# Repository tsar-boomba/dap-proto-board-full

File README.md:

# Bomb DAP Full Proto Board

The culmination of all of my learning during the Spring '26 semester. All the way from making a simple dev board for the TAD5212 DAC, to making a RP2350 board, and now this. Everything combined on one 6-layer board.

# V1 Pinouts

- GPIO0 -> PSRAM_CS
- GPIO1 -> npm1300 GPIO0
- GPIO2 -> DISP_IO_ON (level-shifter enable)
- GPIO3 -> Display Backlight
- GPIO4 -> Display SCLK (PIO SPI)
- GPIO5 -> Display MOSI (PIO SPI)
- GPIO6 -> Display MISO (PIO SPI)
- GPIO7 -> Display DC & SDA
- GPIO8 -> Display CS & SCL
- GPIO(9-11) -> Broken out
- GPIO12 -> SD MISO (SPI1)
- GPIO13 -> SD CS
- GPIO14 -> SD SCLK (SPI1)
- GPIO15 -> SD MOSI (SPI1)
- GPIO16 -> npm1300 SDA (I2C0)
- GPIO17 -> npm1300 SCL (I2C0)
- GPIO18 -> SD ON (load switch & level-shifter enable)
- GPIO19 -> TAD GPIO1
- GPIO20 -> TAD SDA (PIO I2C)
- GPIO21 -> TAD SCL (PIO I2C)
- GPIO(22-26) -> Broken out
- GPIO27 -> TAD DIN (PIO I2S)
- GPIO28 -> TAD FSYNC (PIO I2S)
- GPIO29 -> TAD BCLK (PIO I2S)

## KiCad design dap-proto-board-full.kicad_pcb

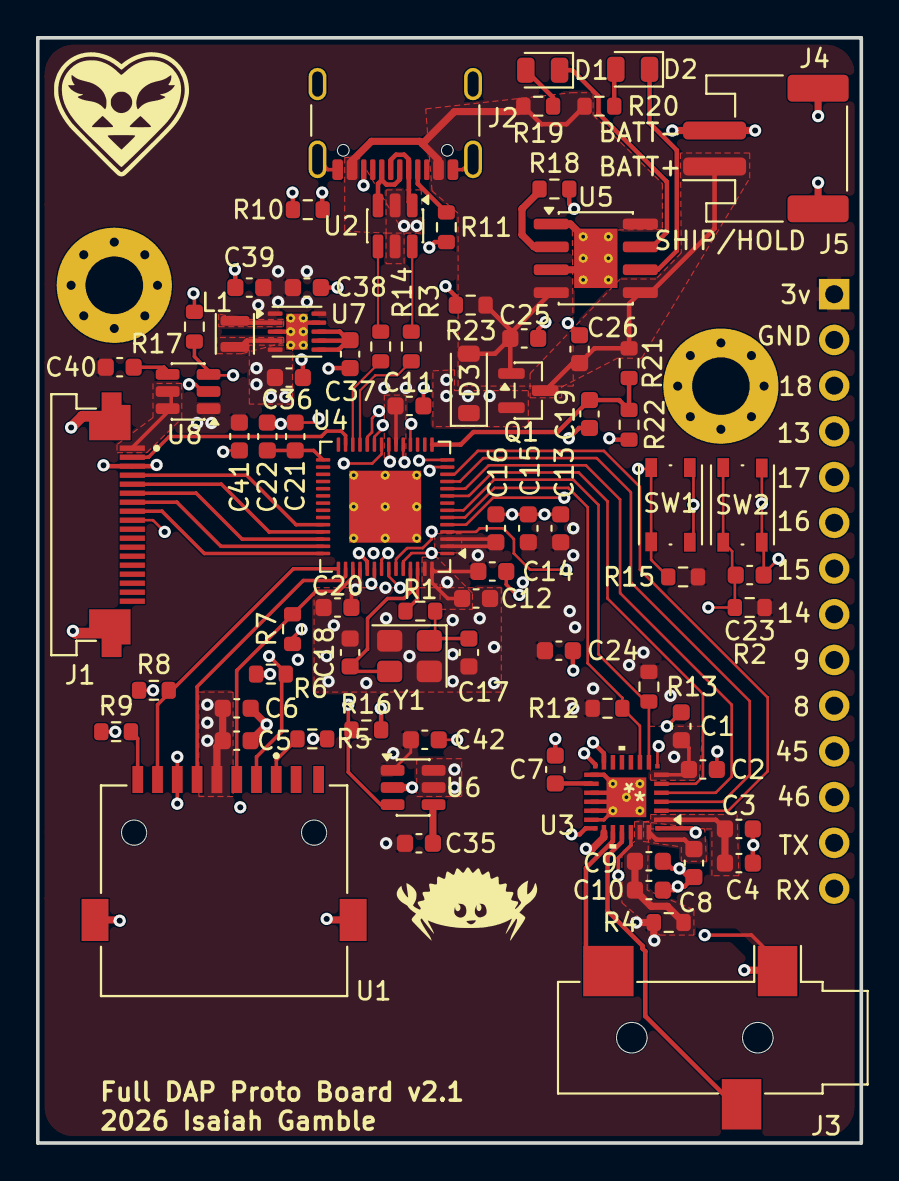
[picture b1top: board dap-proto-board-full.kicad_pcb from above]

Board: 4 copper layers, 45.8 x 61.4 mm, 80 parts (0 on the bottom side), 70 nets.

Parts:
C1, C3, C5, C9, C11, C16, C19, C20, C22, C37: 100nF; C_0603_1608Metric
C2, C4, C6, C10, C24, C26, C38, C39: 10uF; C_0603_1608Metric
C7, C8, C12, C15, C21, C23, C41, C42: 1uF; C_0603_1608Metric
C13: 22uF; C_0603_1608Metric
C14: 10nF; C_0603_1608Metric
C17, C18: 15pF; C_0603_1608Metric
C25, C36: 4.7uF; C_0603_1608Metric
C35, C40: 1nF; C_0603_1608Metric
D1: Yellow; LED_0805_2012Metric
D2: Green; LED_0805_2012Metric
D3: B5819W SL; D_SOD-123
H1, H2: MountingHole_Pad; MountingHole_3.2mm_M3_Pad_Via
J1: SFV18R-1STE1HLF; AMPHENOL_SFV18R-1STE1HLF
J2: UJ20-C-H-G-SMT-1-P16-TR; USB_C_Receptacle_GCT_USB4105-xx-A_16P_TopMnt_Horizontal
J3: SJ-3523-SMT-TR; Jack_3.5mm_CUI_SJ-3523-SMT_Horizontal
J4: S2B-PH-SM4-TB(LF)(SN); JST_PH_S2B-PH-SM4-TB_1x02-1MP_P2.00mm_Horizontal
J5: Conn_01x14; PinSocket_1x14_P2.54mm_Vertical
L1: 1.5uH; L_Murata_DFE201610P
Q1: AO3401A; SOT-23
R1, R4: 0; R_0603_1608Metric
R2, R5, R6, R7, R8, R9, R12, R13, R15, R23: 10k; R_0603_1608Metric
R3, R14: 22; R_0603_1608Metric
R10, R11: 5.1k; R_0603_1608Metric
R16, R17: 100k; R_0603_1608Metric
R18: 3k; R_0603_1608Metric
R19, R20: 1k; R_0603_1608Metric
R21: 1M; R_0603_1608Metric
R22: 470k; R_0603_1608Metric
SW1, SW2: SW_Push; SW_Push_1P1T_NO_Vertical_Wuerth_434133025816
U1: MSD-11-A; CUI_MSD-11-A
U2: USBLC6-2SC6; SOT-23-6
U3: TAD5212; VQFN24_RGE_CORNERPADS_TEX
U4: ESP32-S3FH4R2; QFN-56-1EP_7x7mm_P0.4mm_EP4x4mm_ThermalVias
U5: TP4056-42-ESOP8; SOIC-8-1EP_3.9x4.9mm_P1.27mm_EP2.41x3.3mm_ThermalVias
U6, U8: TPS22917DBVR; SOT-23-6
U7: TPS63031DSKR; WSON-10-1EP_2.5x2.5mm_P0.5mm_EP1.2x2mm_ThermalVias
Y1: TSX-3225 40.0000MF15Y-K3; Crystal_SMD_3225-4Pin_3.2x2.5mm

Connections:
+3V3: C1.2, C2.1, C11.1, C12.1, C13.1, C14.1, C15.1, C16.1, C20.1, C24.1, C35.1, C38.1, C39.1, C40.1, C41.1, C42.1, J5.1, R2.1, R4.1, R12.1, R13.1, R15.1, U3.6 (IOVDD), U4.2 (VDD3P3), U4.3 (VDD3P3), U4.20 (VDD3P3_RTC), U4.46 (VDD3P3_CPU), U4.55 (VDDA), U4.56 (VDDA), U6.1 (VIN), U7.1 (VOUT), U7.10 (FB), U8.1 (VIN)
+BATT: C26.1, J4.1, Q1.3 (D), R21.1, U5.5 (BAT)
/BATT_SENSE: C19.1, R21.2, R22.1, U4.15 (GPIO10)
/BCLK: U3.2 (BCLK), U4.12 (GPIO7)
/DIN: U3.5 (DIN), U4.9 (GPIO4)
/DISP_ON: R17.1, U4.22 (XTAL_32K_N), U8.3 (ON)
/DOUT: U3.4 (DOUT), U4.10 (GPIO5)
/DREG: C3.2, C4.1, U3.1 (DREG)
/FSYNC: U3.3 (FSYNC), U4.11 (GPIO6)
/GPIO8: J5.10, U4.13 (GPIO8)
/GPIO9: J5.9, U4.14 (GPIO9)
/GPIO13: J5.4, U4.18 (GPIO13)
/GPIO14: J5.8, U4.19 (GPIO14)
/GPIO17: J5.5, U4.23 (GPIO17)
/GPIO18: J5.3, U4.24 (GPIO18)
/GPIO45: J5.11, U4.51 (GPIO45)
/GPIO46: J5.12, U4.52 (GPIO46)
/OUT1P: J3.T, U3.20 (OUT1P)
/OUT2P: J3.R, U3.21 (OUT2P)
/SD_CS: R6.2, U1.2 (CS), U4.47 (MTDI)
/SD_DAT1: R9.2, U1.8 (DAT1)
/SD_DAT2: R5.2, U1.1 (DAT2)
/SD_DIN: R7.2, U1.3 (DATA_IN), U4.45 (MTDO)
/SD_DOUT: R8.2, U1.7 (DATA_OUT), U4.43 (GPIO38)
/SD_ON: R16.1, U4.48 (MTMS), U6.3 (ON)
/SD_SCLK: U1.5 (SCLK), U4.44 (MTCK)
/UART_RX: J5.14, U4.50 (U0RXD)
/UART_TX: J5.13, U4.49 (U0TXD)
/USB_D+: R14.1, U2.4 (I/O2)
/USB_D-: R3.1, U2.6 (I/O1)
/XIN: C18.1, U4.53 (XTAL_N), Y1.3
/XOUT: R1.1, U4.54 (XTAL_P)
/disp_CS: J1.9, U4.21 (XTAL_32K_P)
/disp_DC: J1.7, U4.41 (GPIO36)
/disp_LITE: J1.2, U4.27 (GPIO21)
/disp_MISO: J1.6, U4.40 (GPIO35)
/disp_MOSI: J1.5, U4.39 (GPIO34)
/disp_RESET: J1.8, U4.42 (GPIO37)
/disp_SCLK: J1.4, U4.38 (GPIO33)
/tad_SCL: R13.2, U3.7 (SCL), U4.7 (GPIO2)
/tad_SDA: R12.2, U3.8 (SDA), U4.6 (GPIO1)
DISP_VCC: J1.1, U8.5 (QOD), U8.6 (VOUT)
GND: C1.1, C2.2, C3.1, C4.2, C5.2, C6.2, C7.2, C8.2, C9.1, C10.1, C11.2, C12.2, C13.2, C14.2, C15.2, C16.2, C17.2, C18.2, C19.2, C20.2, C21.2, C22.2, C23.2, C24.2, C25.2, C26.2, C36.2, C37.2, C38.2, C39.2, C41.2, C42.2, H1.1 (1_1), H2.1 (1_1), J1.3, J1.MP (MountPin), J2.A1 (GND), J2.A12 (GND), J2.B1 (GND), J2.B12 (GND), J2.SH (SHIELD), J4.2, J4.MP (MountPin), J5.2, J5.6, J5.7, R10.2, R11.2, R16.2, R17.2, R18.2, R22.2, R23.2, SW1.1, SW2.2, U1.6 (VSS), U1.SH, U2.2 (GND), U3.12 (GPI1), U3.13 (ADDR), U3.15 (IN1P), U3.16 (IN1M), U3.17 (IN2P), U3.18 (IN2M), U3.29 (EPAD), U3.A1 (VSS), U3.A2 (VSS), U3.A3 (VSS), U3.A4 (VSS), U4.57 (GND), U5.1 (TEMP), U5.3 (GND), U5.9 (EPAD), U6.2 (GND), U7.3 (PGND), U7.9 (GND), U7.11 (PGND), U8.2 (GND), Y1.2, Y1.4
unnamed: C17.1, R1.2, Y1.1
unnamed: D1.2 (A), R19.2
unnamed: D1.1 (K), U5.7 (~CHRG)
unnamed: D2.2 (A), R20.2
unnamed: D2.1 (K), U5.6 (~STDBY)
unnamed: J2.A5 (CC1), R11.1
unnamed: J2.B5 (CC2), R10.1
unnamed: J2.A6 (D+), J2.B6 (D+), U2.3 (I/O2)
unnamed: J2.A7 (D-), J2.B7 (D-), U2.1 (I/O1)
unnamed: C9.2, C10.2, R4.2, U3.23 (AVDD)
unnamed: C7.1, U3.14 (MICBIAS)
unnamed: C8.1, U3.24 (VREF)
unnamed: C23.1, R2.2, SW2.1, U4.4 (CHIP_PU)
unnamed: R15.2, SW1.2, U4.5 (GPIO0)
unnamed: R3.2, U4.25 (GPIO19/USB_D-)
unnamed: R14.2, U4.26 (GPIO20/USB_D+)
unnamed: C21.1, C22.1, U4.29 (VDD_SPI)
unnamed: R18.1, U5.2 (PROG)
unnamed: C35.2, U6.4 (CT)
unnamed: C37.1, U7.6 (EN), U7.7 (PS/SYNC), U7.8 (VINA)
unnamed: L1.1, U7.4 (L1)
unnamed: L1.2, U7.2 (L2)
unnamed: C40.2, U8.4 (CT)
SD_VCC: C5.1, C6.1, R5.1, R6.1, R7.1, R8.1, R9.1, U1.4 (VDD), U6.5 (QOD), U6.6 (VOUT)
VBUS: C25.1, D3.2 (A), J2.A4 (VBUS), J2.A9 (VBUS), J2.B4 (VBUS), J2.B9 (VBUS), Q1.1 (G), R19.1, R20.1, R23.1, U2.5 (VBUS), U5.4 (V_{CC}), U5.8 (CE)
VCOM: J3.S, U3.19 (OUT1M), U3.22 (OUT2M)
VSYS: C36.1, D3.1 (K), Q1.2 (S), U7.5 (VIN)

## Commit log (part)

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2026-04-23 kinda v1
2026-04-25 make ground plane solid + docs
2026-04-25 add readme.md
2026-04-26 decrease min width of ground fill around crystal
2026-05-22 I forgort what I did
2026-06-09 mostly finished; just need to breakout extra gpio
2026-06-10 breakout extra gpios; gen gerbers and images
